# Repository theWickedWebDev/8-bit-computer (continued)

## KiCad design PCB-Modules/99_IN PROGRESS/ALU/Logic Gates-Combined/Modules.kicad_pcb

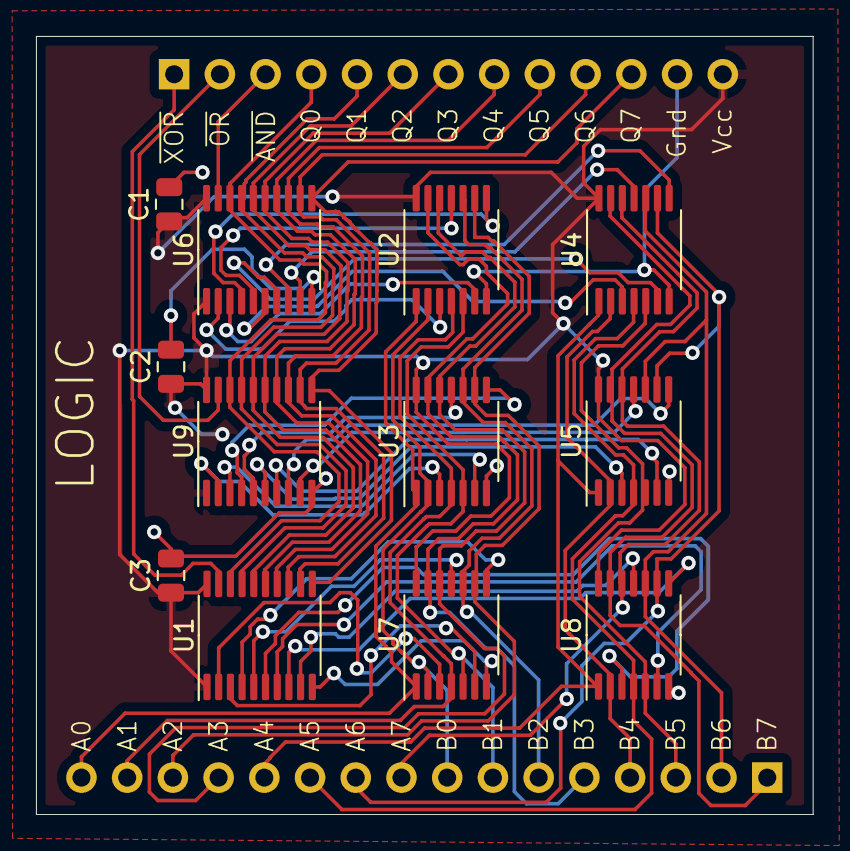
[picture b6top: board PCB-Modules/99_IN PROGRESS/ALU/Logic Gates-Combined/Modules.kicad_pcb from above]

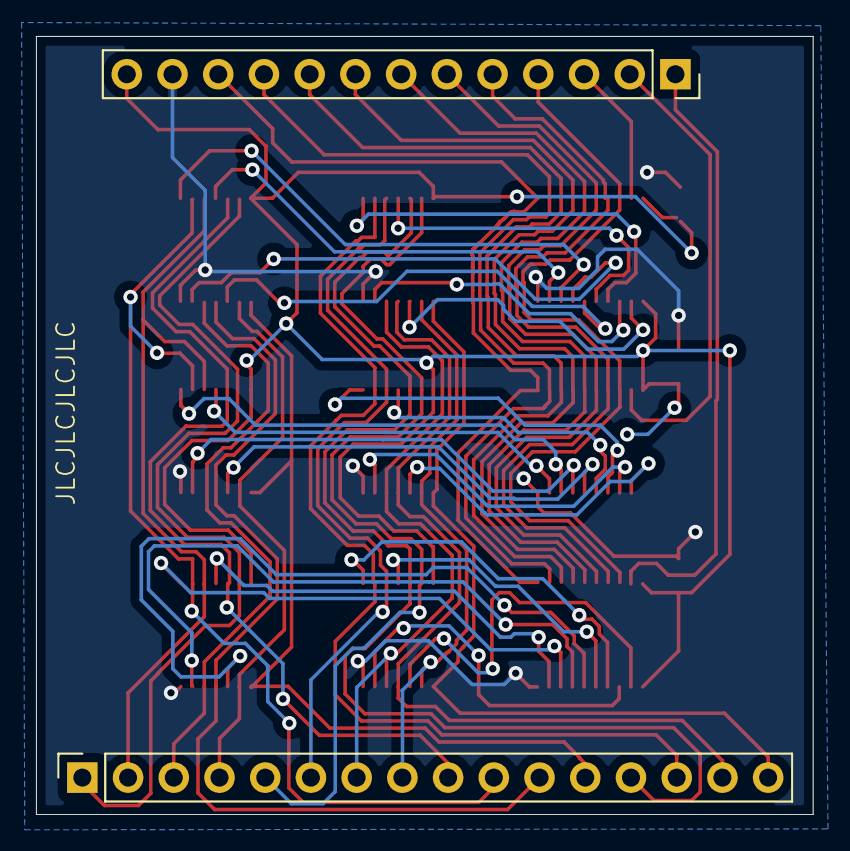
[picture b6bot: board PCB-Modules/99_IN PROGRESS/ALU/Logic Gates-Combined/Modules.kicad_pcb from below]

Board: 2 copper layers, 43.2 x 43.2 mm, 14 parts (2 on the bottom side), 53 nets.

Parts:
C1, C2, C3: C; C_0805_2012Metric
J1: Conn_01x16; PinSocket_1x16_P2.54mm_Vertical
JC: Conn_01x13; PinSocket_1x13_P2.54mm_Vertical
U1, U6, U9: 74LS245; TSSOP-20_4.4x6.5mm_P0.65mm
U2, U4: 74LS08; TSSOP-14_4.4x5mm_P0.65mm
U3, U5: 74LS32; TSSOP-14_4.4x5mm_P0.65mm
U7, U8: 74LS86; TSSOP-14_4.4x5mm_P0.65mm

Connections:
A0: J1.16, U2.1, U3.1, U7.1
A1: J1.15, U2.4, U3.4, U7.4
A2: J1.14, U2.9, U3.9, U7.9
A3: J1.13, U2.12, U3.12, U7.12
A4: J1.12, U4.1, U5.1, U8.1
A5: J1.11, U4.4, U5.4, U8.4
A6: J1.10, U4.9, U5.9, U8.9
A7: J1.9, U4.12, U5.12, U8.12
B0: J1.8, U2.2, U3.2, U7.2
B1: J1.7, U2.5, U3.5, U7.5
B2: J1.6, U2.10, U3.10, U7.10
B3: J1.5, U2.13, U3.13, U7.13
B4: J1.4, U4.2, U5.2, U8.2
B5: J1.3, U4.5, U5.5, U8.5
B6: J1.2, U4.10, U5.10, U8.10
B7: J1.1, U4.13, U5.13, U8.13
GND: C1.2, C2.2, C3.2, JC.12, U1.10 (GND), U2.7 (GND), U3.7 (GND), U4.7 (GND), U5.7 (GND), U6.10 (GND), U7.7 (GND), U8.7 (GND), U9.10 (GND)
unnamed: U1.2 (A0), U7.3
unnamed: U3.3, U9.2 (A0)
unnamed: U3.6, U9.3 (A1)
unnamed: U3.8, U9.4 (A2)
unnamed: U3.11, U9.5 (A3)
unnamed: U5.3, U9.6 (A4)
unnamed: U5.6, U9.7 (A5)
unnamed: U5.8, U9.8 (A6)
unnamed: U5.11, U9.9 (A7)
unnamed: U2.3, U6.2 (A0)
unnamed: U2.6, U6.3 (A1)
unnamed: U2.8, U6.4 (A2)
unnamed: U2.11, U6.5 (A3)
unnamed: U4.3, U6.6 (A4)
unnamed: U4.6, U6.7 (A5)
unnamed: U4.8, U6.8 (A6)
unnamed: U4.11, U6.9 (A7)
unnamed: U1.3 (A1), U7.6
unnamed: U1.4 (A2), U7.8
unnamed: U1.5 (A3), U7.11
unnamed: U1.6 (A4), U8.3
unnamed: U1.7 (A5), U8.6
unnamed: U1.8 (A6), U8.8
unnamed: U1.9 (A7), U8.11
Q0: JC.4, U1.18 (B0), U6.18 (B0), U9.18 (B0)
Q1: JC.5, U1.17 (B1), U6.17 (B1), U9.17 (B1)
Q2: JC.6, U1.16 (B2), U6.16 (B2), U9.16 (B2)
Q3: JC.7, U1.15 (B3), U6.15 (B3), U9.15 (B3)
Q4: JC.8, U1.14 (B4), U6.14 (B4), U9.14 (B4)
Q5: JC.9, U1.13 (B5), U6.13 (B5), U9.13 (B5)
Q6: JC.10, U1.12 (B6), U6.12 (B6), U9.12 (B6)
Q7: JC.11, U1.11 (B7), U6.11 (B7), U9.11 (B7)
VCC: C1.1, C2.1, C3.1, JC.13, U1.1 (A->B), U1.20 (VCC), U2.14 (VCC), U3.14 (VCC), U4.14 (VCC), U5.14 (VCC), U6.1 (A->B), U6.20 (VCC), U7.14 (VCC), U8.14 (VCC), U9.1 (A->B), U9.20 (VCC)
~AND: JC.3, U6.19 (CE)
~OR: JC.2, U9.19 (CE)
~XOR: JC.1, U1.19 (CE)

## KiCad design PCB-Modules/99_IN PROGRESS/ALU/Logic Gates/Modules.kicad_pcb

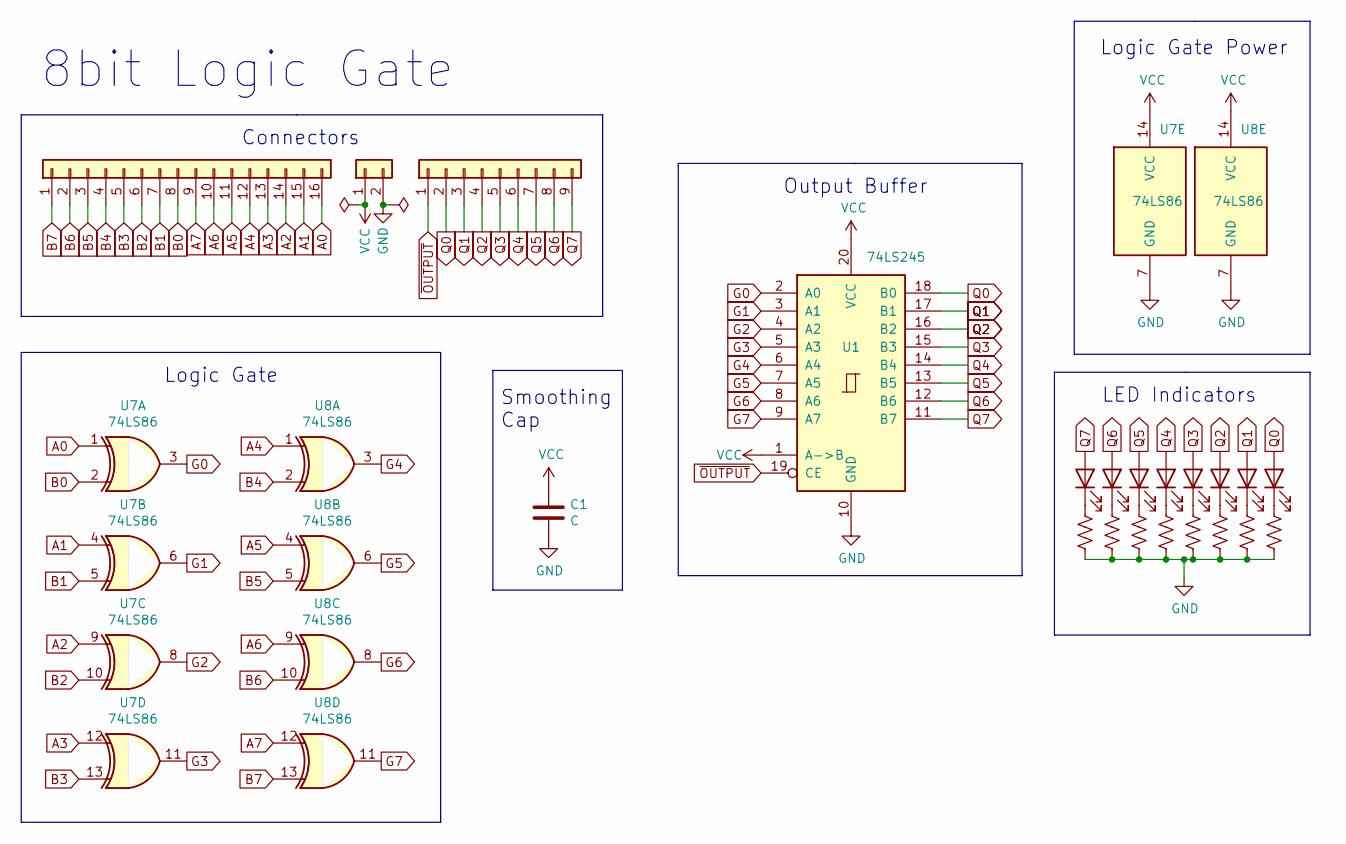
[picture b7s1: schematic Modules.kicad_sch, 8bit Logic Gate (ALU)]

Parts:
C1: C; C_0805_2012Metric
D1, D2, D3, D4, D5, D6, D7, D8: LED; LED_0805_2012Metric
J1: Conn_01x16; PinSocket_1x16_P2.54mm_Vertical
J2: Conn_01x02; PinSocket_1x02_P2.54mm_Vertical
J3: Conn_01x09; PinSocket_1x09_P2.54mm_Vertical
R1, R2, R3, R4, R5, R6, R7, R8: R_US; R_0805_2012Metric
U1: 74LS245; TSSOP-20_4.4x6.5mm_P0.65mm
U7, U8: 74LS86; TSSOP-14_4.4x5mm_P0.65mm

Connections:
A0: J1.16, U7.1
A1: J1.15, U7.4
A2: J1.14, U7.9
A3: J1.13, U7.12
A4: J1.12, U8.1
A5: J1.11, U8.4
A6: J1.10, U8.9
A7: J1.9, U8.12
B0: J1.8, U7.2
B1: J1.7, U7.5
B2: J1.6, U7.10
B3: J1.5, U7.13
B4: J1.4, U8.2
B5: J1.3, U8.5
B6: J1.2, U8.10
B7: J1.1, U8.13
GND: C1.2, J2.2, R1.2, R2.2, R3.2, R4.2, R5.2, R6.2, R7.2, R8.2, U1.10 (GND), U7.7 (GND), U8.7 (GND)
unnamed: D1.1 (K), R1.1
unnamed: D2.1 (K), R2.1
unnamed: D3.1 (K), R3.1
unnamed: D4.1 (K), R4.1
unnamed: D5.1 (K), R5.1
unnamed: D6.1 (K), R6.1
unnamed: D7.1 (K), R7.1
unnamed: D8.1 (K), R8.1
unnamed: U1.2 (A0), U7.3
unnamed: U1.3 (A1), U7.6
unnamed: U1.4 (A2), U7.8
unnamed: U1.5 (A3), U7.11
unnamed: U1.6 (A4), U8.3
unnamed: U1.7 (A5), U8.6
unnamed: U1.8 (A6), U8.8
unnamed: U1.9 (A7), U8.11
Q0: D8.2 (A), J3.2, U1.18 (B0)
Q1: D7.2 (A), J3.3, U1.17 (B1)
Q2: D6.2 (A), J3.4, U1.16 (B2)
Q3: D5.2 (A), J3.5, U1.15 (B3)
Q4: D4.2 (A), J3.6, U1.14 (B4)
Q5: D3.2 (A), J3.7, U1.13 (B5)
Q6: D2.2 (A), J3.8, U1.12 (B6)
Q7: D1.2 (A), J3.9, U1.11 (B7)
VCC: C1.1, J2.1, U1.1 (A->B), U1.20 (VCC), U7.14 (VCC), U8.14 (VCC)
~OUTPUT: J3.1, U1.19 (CE)

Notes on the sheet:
LED Indicators
8bit Logic Gate
Logic Gate Power
Smoothing Cap
Connectors
Logic Gate
Output Buffer

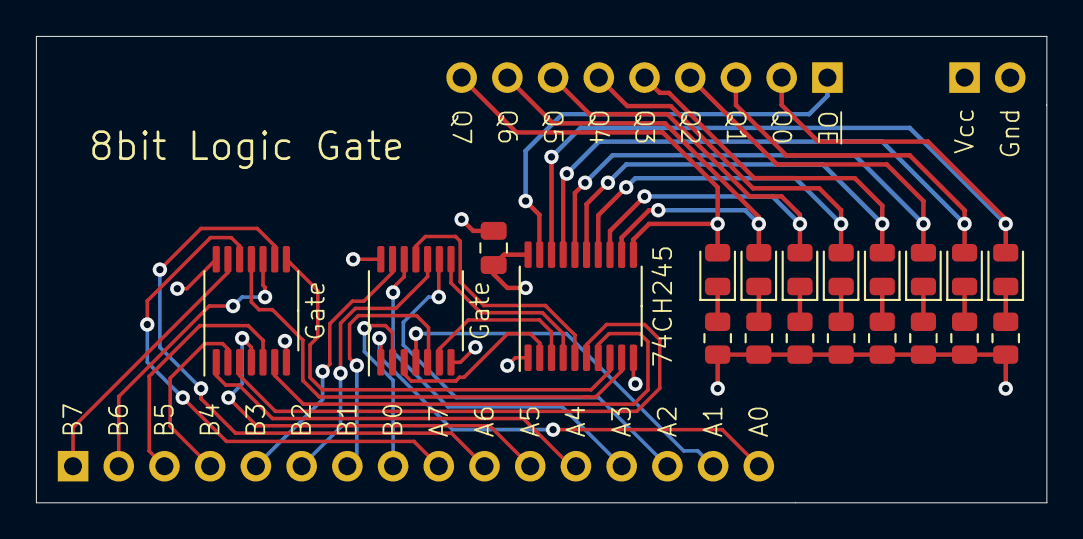
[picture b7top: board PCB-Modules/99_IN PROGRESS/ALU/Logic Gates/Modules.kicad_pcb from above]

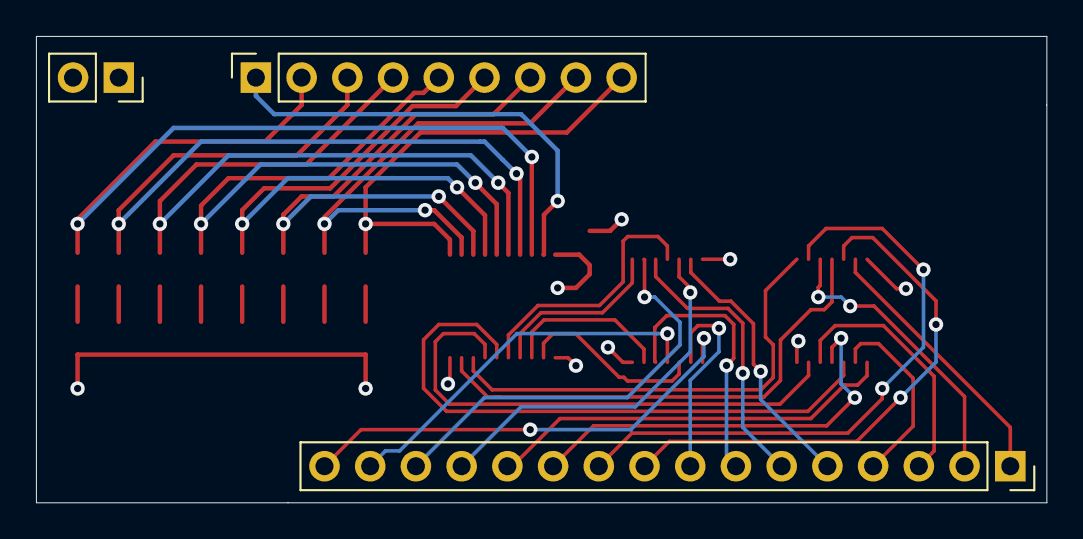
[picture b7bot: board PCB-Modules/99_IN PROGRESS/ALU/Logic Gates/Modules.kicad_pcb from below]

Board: 4 copper layers, 56.1 x 25.9 mm, 23 parts (3 on the bottom side), 43 nets.

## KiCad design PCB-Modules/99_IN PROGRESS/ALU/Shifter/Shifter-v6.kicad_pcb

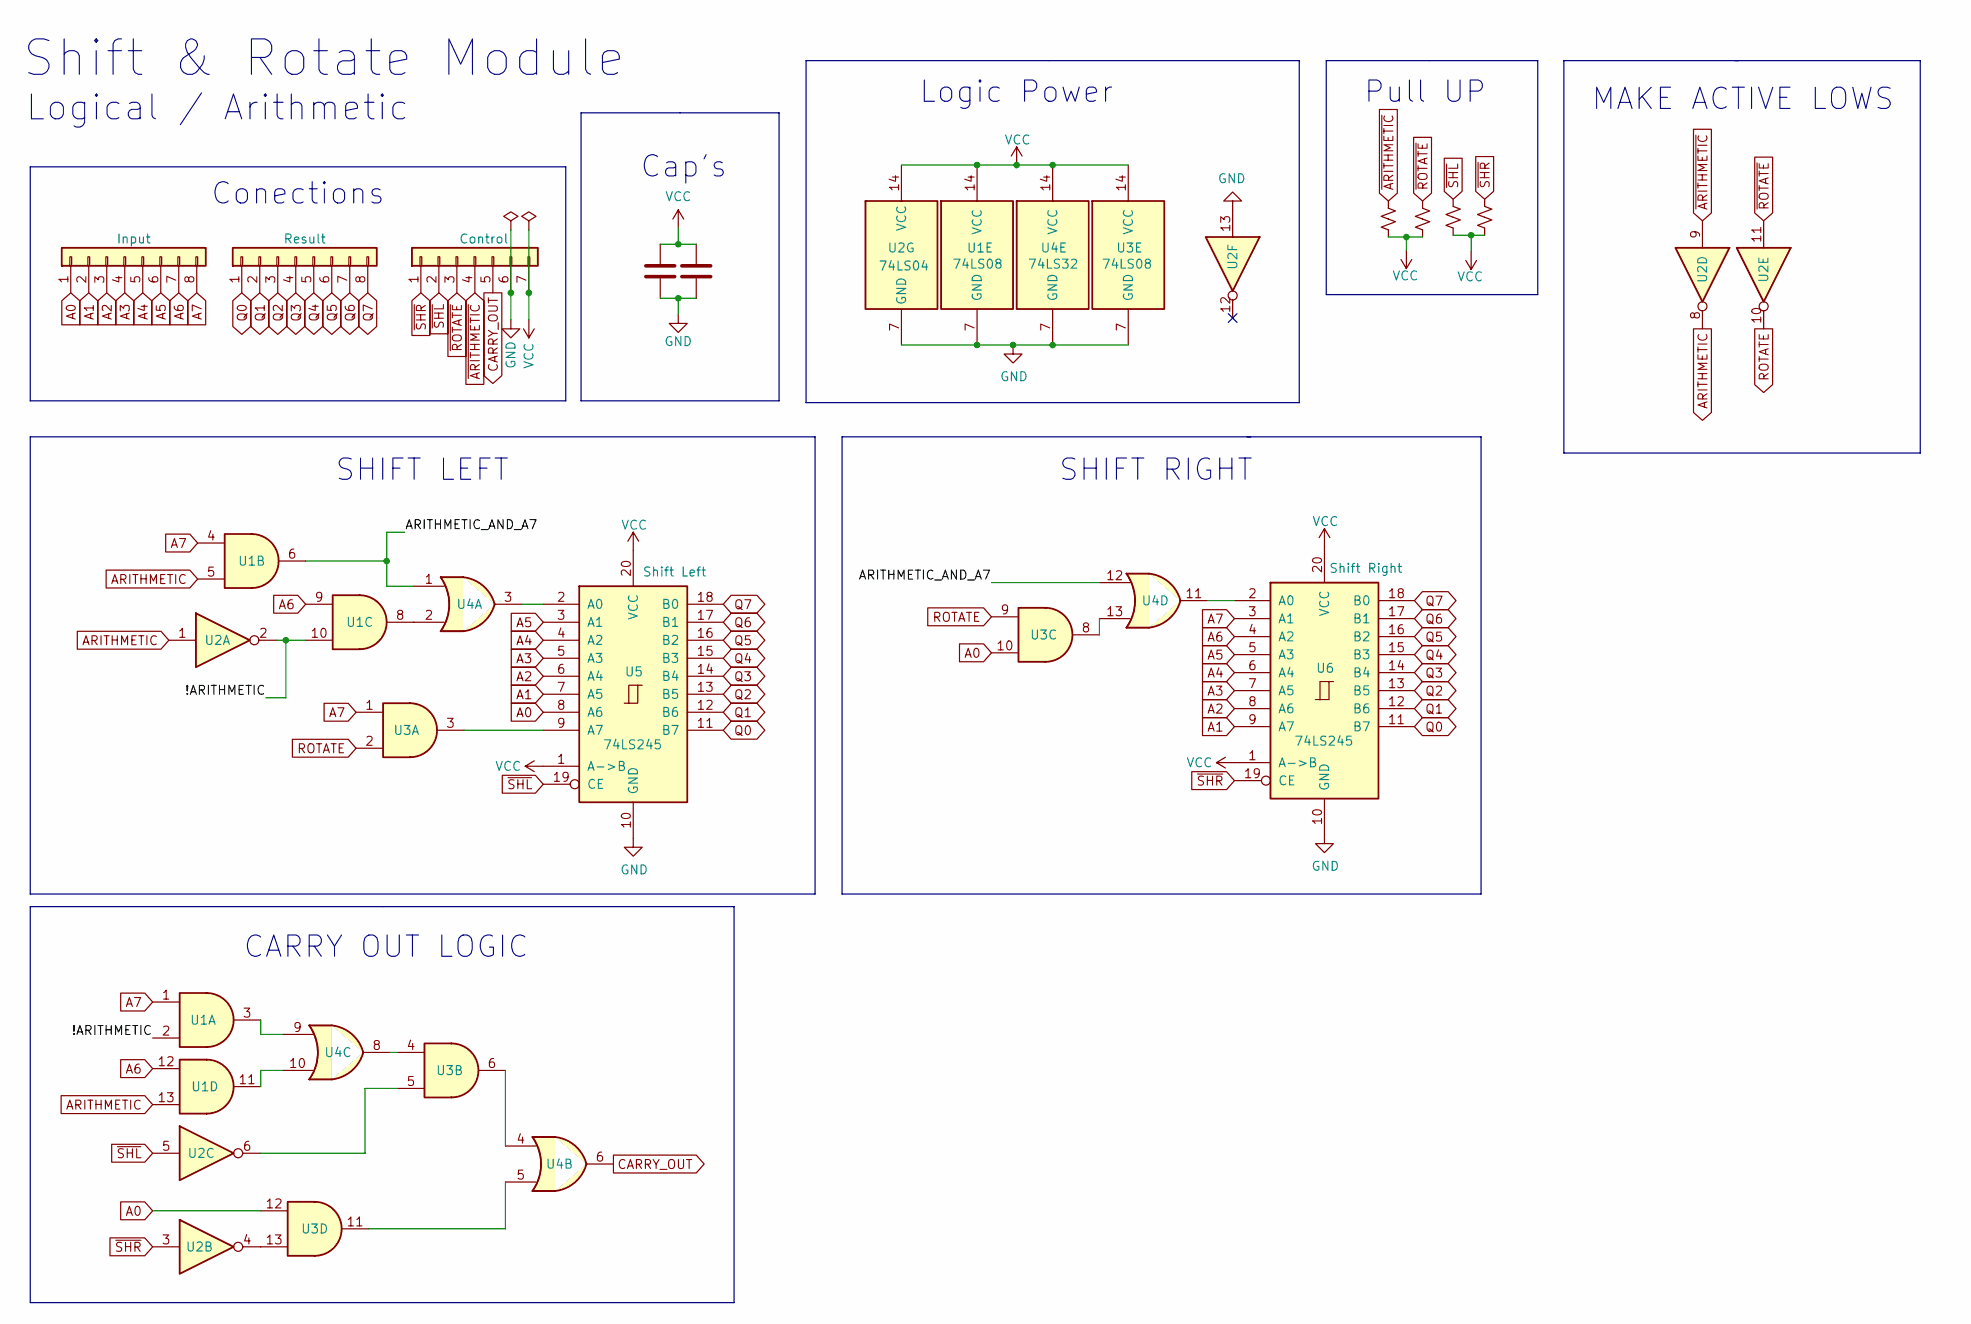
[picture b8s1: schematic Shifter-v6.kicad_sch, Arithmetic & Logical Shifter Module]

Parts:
C1, C2: C; C_0805_2012Metric
J1, J2: Conn_01x08; PinHeader_1x08_P2.54mm_Vertical
J3: Conn_01x07; PinHeader_1x07_P2.54mm_Vertical
R10, R11, R12, R13: R_Small_US; R_0805_2012Metric
U1, U3: 74LS08; TSSOP-14_4.4x5mm_P0.65mm
U2: 74LS04; TSSOP-14_4.4x5mm_P0.65mm
U4: 74LS32; TSSOP-14_4.4x5mm_P0.65mm
U5, U6: 74LS245; TSSOP-20_4.4x5mm_P0.5mm

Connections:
/!ARITHMETIC: U1.2, U1.10, U2.2
/ARITHMETIC_AND_A7: U1.6, U4.1, U4.12
A0: J1.1, U3.10, U3.12, U5.8 (A6)
A1: J1.2, U5.7 (A5), U6.9 (A7)
A2: J1.3, U5.6 (A4), U6.8 (A6)
A3: J1.4, U5.5 (A3), U6.7 (A5)
A4: J1.5, U5.4 (A2), U6.6 (A4)
A5: J1.6, U5.3 (A1), U6.5 (A3)
A6: J1.7, U1.9, U1.12, U6.4 (A2)
A7: J1.8, U1.1, U1.4, U3.1, U6.3 (A1)
ARITHMETIC: U1.5, U1.13, U2.1, U2.8
CARRY_OUT: J3.5, U4.6
GND: C1.1, C2.1, J3.6, U1.7 (GND), U2.7 (GND), U2.13, U3.7 (GND), U4.7 (GND), U5.10 (GND), U6.10 (GND)
unnamed: U1.3, U4.9
unnamed: U1.8, U4.2
unnamed: U1.11, U4.10
unnamed: U2.4, U3.13
unnamed: U2.6, U3.5
unnamed: U3.3, U5.9 (A7)
unnamed: U3.4, U4.8
unnamed: U3.6, U4.4
unnamed: U3.8, U4.13
unnamed: U3.11, U4.5
unnamed: U4.3, U5.2 (A0)
unnamed: U4.11, U6.2 (A0)
Q0: J2.1, U5.11 (B7), U6.11 (B7)
Q1: J2.2, U5.12 (B6), U6.12 (B6)
Q2: J2.3, U5.13 (B5), U6.13 (B5)
Q3: J2.4, U5.14 (B4), U6.14 (B4)
Q4: J2.5, U5.15 (B3), U6.15 (B3)
Q5: J2.6, U5.16 (B2), U6.16 (B2)
Q6: J2.7, U5.17 (B1), U6.17 (B1)
Q7: J2.8, U5.18 (B0), U6.18 (B0)
ROTATE: U2.10, U3.2, U3.9
~ARITHMETIC: J3.4, R13.1, U2.9
~ROTATE: J3.3, R10.1, U2.11
~SHL: J3.2, R11.1, U2.5, U5.19 (CE)
~SHR: J3.1, R12.1, U2.3, U6.19 (CE)

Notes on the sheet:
Cap's
Shift & Rotate Module
SHIFT RIGHT
SHIFT LEFT
Conections
Logic Power
MAKE ACTIVE LOWS
Pull UP
Logical / Arithmetic
CARRY OUT LOGIC

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
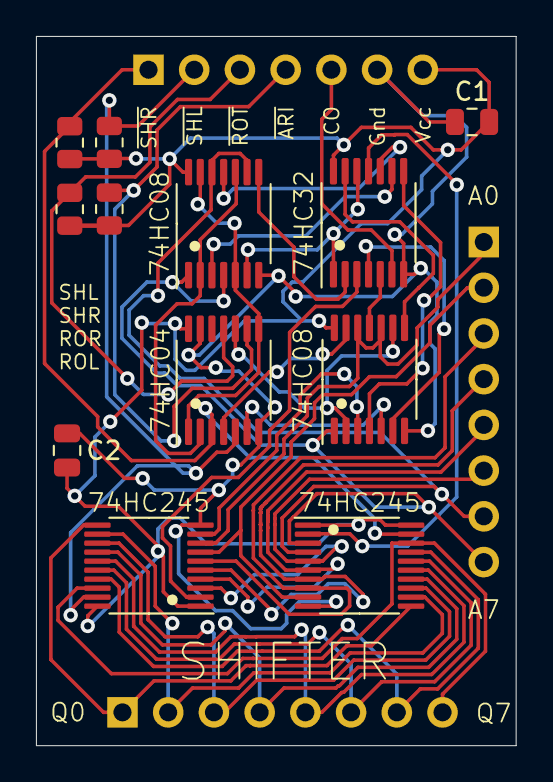
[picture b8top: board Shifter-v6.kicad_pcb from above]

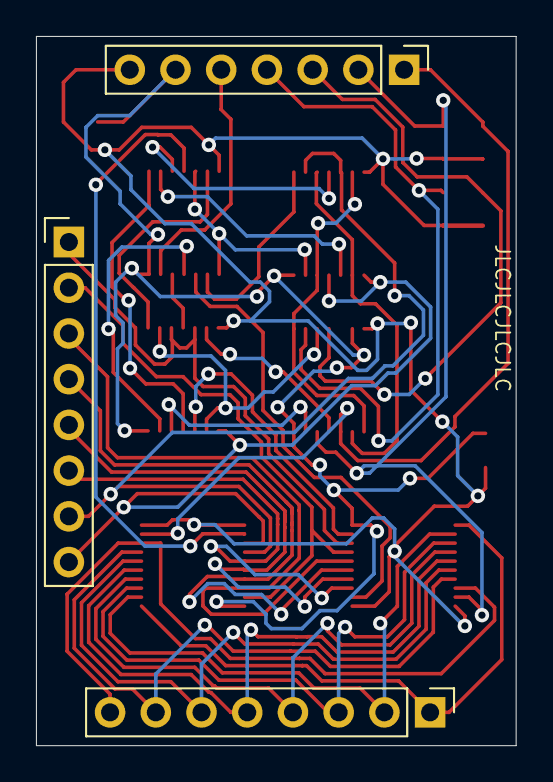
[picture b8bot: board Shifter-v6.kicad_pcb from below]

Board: 2 copper layers, 26.7 x 39.4 mm, 15 parts (3 on the bottom side), 39 nets.
